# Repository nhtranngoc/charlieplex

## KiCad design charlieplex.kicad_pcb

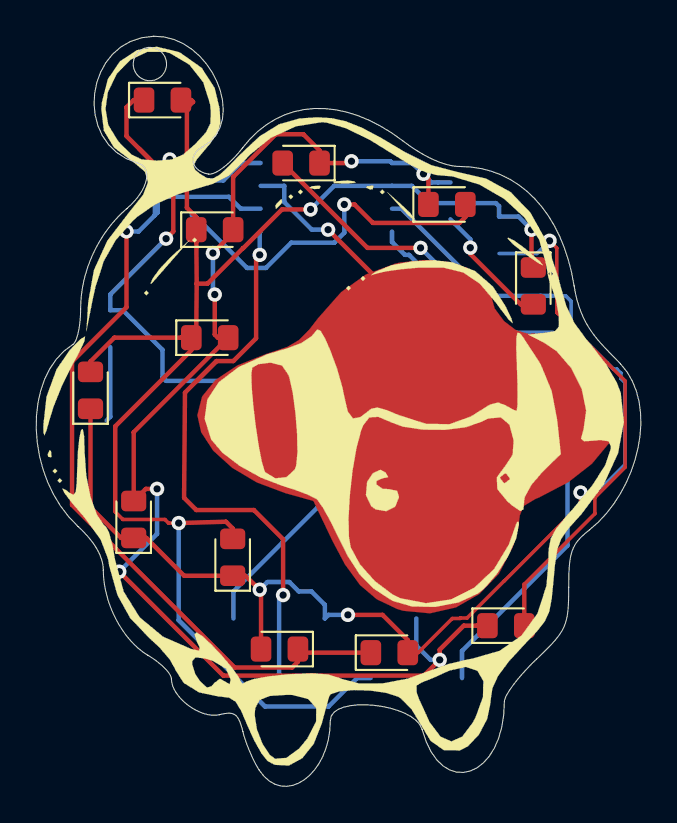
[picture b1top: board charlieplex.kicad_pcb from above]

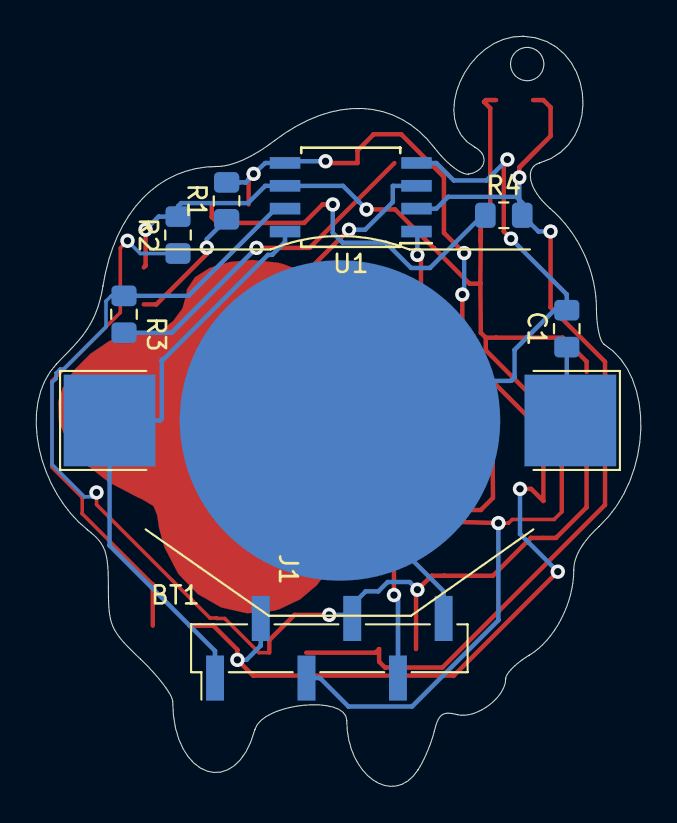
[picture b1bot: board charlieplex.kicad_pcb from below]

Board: 2 copper layers, 33.6 x 41.6 mm, 21 parts (8 on the bottom side), 11 nets.

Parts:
BT1: Battery_Cell; BatteryHolder_Keystone_3002_1x2032
C1: 0.1uF; C_0805_2012Metric_Pad1.15x1.40mm_HandSolder
D1, D2, D3, D4, D5, D6, D7, D8, D9, D10, D11, D12: LED; LED_0805_2012Metric_Pad1.15x1.40mm_HandSolder
J1: ISP; PinHeader_1x06_P2.54mm_Vertical_SMD_Pin1Left
J2: TouchPad; touchpad2
R1, R2, R3, R4: 220R; R_0805_2012Metric_Pad1.15x1.40mm_HandSolder
U1: SOIJ-8_5.3x5.3mm_P1.27mm

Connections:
GND: BT1.2, C1.2, J1.6, U1.4
unnamed: D1.2, R2.1
unnamed: D2.2, R3.1
unnamed: D3.2, R4.1
unnamed: D4.2, R1.1
PB0: D1.1, D2.1, D3.1, D5.2, D6.2, D8.2, J1.2, R1.2, U1.5
PB1: D4.1, D5.1, D6.1, D7.2, D9.2, D12.2, J1.3, R2.2, U1.6
PB2: D7.1, D8.1, D9.1, D10.2, D11.2, J1.4, R3.2, U1.7
PB3: D10.1, D11.1, D12.1, R4.2, U1.2
RST: J1.5, U1.1
VCC: BT1.1, C1.1, J1.1, U1.8

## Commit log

2020-07-24 Added picture
